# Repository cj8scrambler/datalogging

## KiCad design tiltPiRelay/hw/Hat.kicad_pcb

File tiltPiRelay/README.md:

# TiltPiRelay
Temp controller relay which uses DS18B20 temp sensors and Tilt hydrometers to monitor temperature, control power relays and log data at adafruit.io.  This is intended for a temp controller and data logger for beer fermentation.  It can control 2 seperate fermentations and also monitor internal, ambient and glycol temperatures.  It's written as a python script and intended to run on a Raspberry Pi.

## Hardware

### Relay Board
The controller uses an [off the shelf 4-relay Pi HAT](https://www.amazon.com/gp/product/B072XGF4Z3).  The 4 relays allow for 3 states (Heat/Cold/Off) for each of the two monitored channels.

### LCD / Rotary Encoder / LEDs
The [rotary encoder](https://www.adafruit.com/product/4991) used from Adafruit includes a controller and RGB LED which can be accessed by I2C.  The LCD is a HD44780 based 16x2 I2C display.  All the I2C devices can be daisy chained together.  To simplify the wiring, an interposer HAT was created which adds qwiic connectors.

### Temp sensors
There are 5 one-wire-bus temp sensors supported:
  * Channel 1 - Temperature of fermentation 1 (Used for temp control)
  * Channel 2 - Temperature of fermentation 2 (Used for temp control)
  * Ambient - Ambient air temperature (logged and displayed)
  * Glycol - Glycol reserve temperature (logged and displayed)
  * Internal - Internal temperature on the HAT interposer

Each temp sensor is expected to be on it's own bus (GPIO).  This way there is no need to figure out the address of each sensor.  A 3.5mm stereo headset connector is used to make the temperature probes removeable.

### Connector Interposer
An interposer board simplifies connecting the 1-wire bus temp sensors and I2C deices.  Design files:
  * [Schematic](hw/schematic.pdf) PDF
  * KiCAD design files
    * [Project](hhw/Hat.kicad_pro)
    * [Schematic](hw/Hat.kicad_sch)
    * [PCB](h2/Hat.kicad_pcb)

### Assembly
Inside assembly without high voltage connected

## Software

### One time setup
The dependent Python packages need to be available.  One way to do that is with a virtual env:
```
sudo apt-get install python3-dev
python3 -m venv .venv
. ./.venv/bin/activate
pip3 install --upgrade pip setuptools wheel 
pip3 install -r requirements.txt

. ./.venv/bin/activate
CFLAGS="-fcommon"  pip3 install RPi.GPIO
```

### BLE Support
To receive Tilt hydrometer data, you'll need a BLE capable bluetooth controller.  The Tilt hydrometer sends data in repeated BLE advertisements.  As of September 2024, the bleak packaged should receive these correctly.

On older setups, repeated BLE advertisements would not be reported by bleak.  The workaround was to use hcidump, but this required [special configuration](https://github.com/adafruit/Adafruit_Blinka_bleio#support-for-duplicate-advertisement-scanning-on-linux) so that a regular user can run hcidump.  If you don't see any Tilt data coming in, make sure your user has permissions to run hcidump.

### Load w1 busses
The 5 W1 busses need to be started in order so that the script knows which bus is which temp sensor.  This can be done with `w1-setup.sh load` or manuall done with:
```
sudo dtoverlay w1-gpio gpiopin=23 pullup=0  # CTRL-1  (top left)
sudo dtoverlay w1-gpio gpiopin=27 pullup=0  # CTRL-2  (top right)
sudo dtoverlay w1-gpio gpiopin=17 pullup=0  # AMBIENT (top middle)
sudo dtoverlay w1-gpio gpiopin=24 pullup=0  # GLYCOL  (bottom middle)
sudo dtoverlay w1-gpio gpiopin=25 pullup=0  # ONBOARD
```

### Start at boot
A simple systemd service is defined to auto-start at boot.  Install it with:
```
sudo cp tiltpirelay.service /usr/lib/systemd/system/
sudo systemctl enable tiltpirelay
```

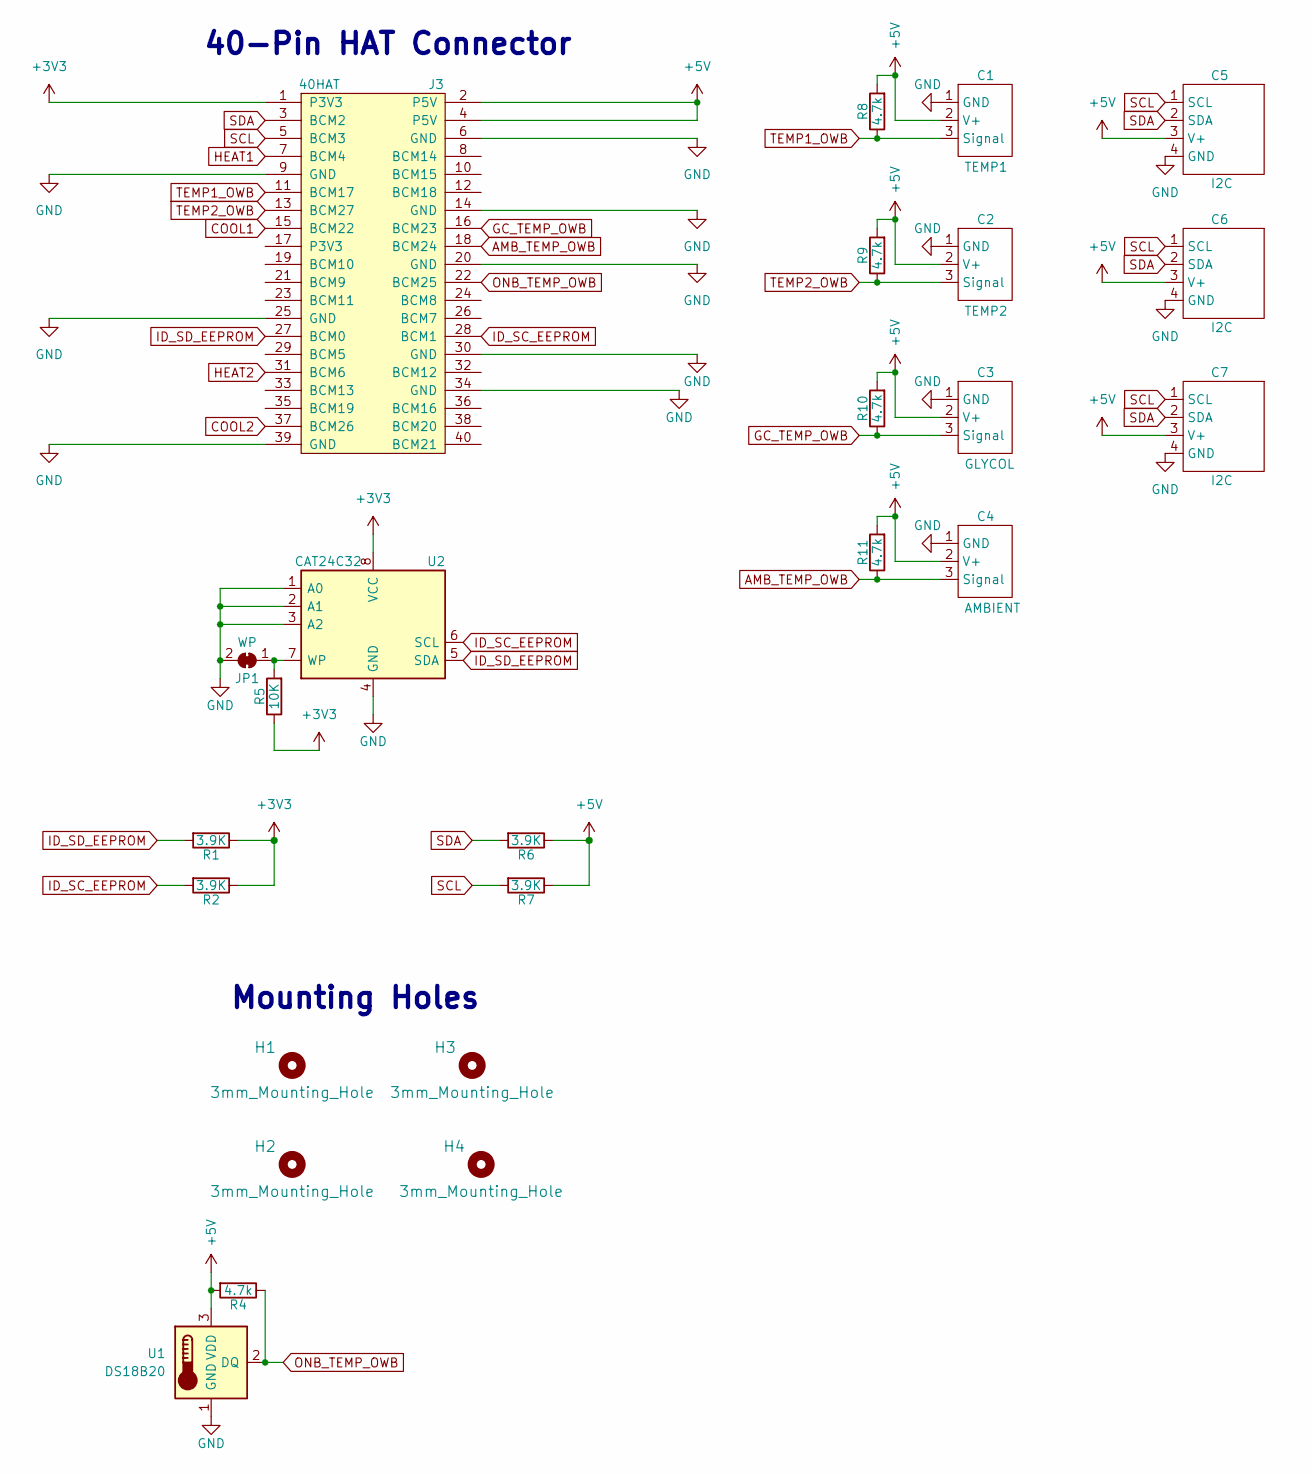
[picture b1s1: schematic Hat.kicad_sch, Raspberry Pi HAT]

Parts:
C1: TEMP1; JST_PH_S3B-PH-SM4-TB_1x03-1MP_P2.00mm_Horizontal
C2: TEMP2; JST_PH_S3B-PH-SM4-TB_1x03-1MP_P2.00mm_Horizontal
C3: GLYCOL; JST_PH_S3B-PH-SM4-TB_1x03-1MP_P2.00mm_Horizontal
C4: AMBIENT; JST_PH_S3B-PH-SM4-TB_1x03-1MP_P2.00mm_Horizontal
C5, C6, C7: I2C; JST_PH_S4B-PH-SM4-TB_1x04-1MP_P2.00mm_Horizontal
H1, H2, H3, H4: 3mm_Mounting_Hole; NPTH_3mm_ID
J3: 40HAT; PinSocket_2x20_P2.54mm_Vertical
JP1: WP; SolderJumper-2_P1.3mm_Bridged_Pad1.0x1.5mm
R1, R2, R6, R7: 3.9K; R_0603_1608Metric
R4, R8, R9, R10, R11: 4.7k; R_0603_1608Metric
R5: 10K; R_0603_1608Metric
U1: DS18B20; TO-92_Inline
U2: CAT24C32; SOIC-8_3.9x4.9mm_P1.27mm

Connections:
+3V3: J3.1 (P3V3), R1.1, R2.1, R5.1, U2.8 (VCC)
+5V: C1.2 (V+), C2.2 (V+), C3.2 (V+), C4.2 (V+), C5.3 (V+), C6.3 (V+), C7.3 (V+), J3.2 (P5V), J3.4 (P5V), R4.2, R6.1, R7.1, R8.2, R9.2, R10.2, R11.2, U1.3 (VDD)
AMB_TEMP_OWB: C4.3 (Signal), J3.18 (BCM24), R11.1
COOL1: J3.15 (BCM22)
COOL2: J3.37 (BCM26)
GC_TEMP_OWB: C3.3 (Signal), J3.16 (BCM23), R10.1
GND: C1.1 (GND), C2.1 (GND), C3.1 (GND), C4.1 (GND), C5.4 (GND), C6.4 (GND), C7.4 (GND), J3.6 (GND), J3.9 (GND), J3.14 (GND), J3.20 (GND), J3.25 (GND), J3.30 (GND), J3.34 (GND), J3.39 (GND), JP1.2 (B), U1.1 (GND), U2.1 (A0), U2.2 (A1), U2.3 (A2), U2.4 (GND)
HEAT1: J3.7 (BCM4)
HEAT2: J3.31 (BCM6)
ID_SC_EEPROM: J3.28 (BCM1), R2.2, U2.6 (SCL)
ID_SD_EEPROM: J3.27 (BCM0), R1.2, U2.5 (SDA)
unnamed: JP1.1 (A), R5.2, U2.7 (WP)
ONB_TEMP_OWB: J3.22 (BCM25), R4.1, U1.2 (DQ)
SCL: C5.1 (SCL), C6.1 (SCL), C7.1 (SCL), J3.5 (BCM3), R7.2
SDA: C5.2 (SDA), C6.2 (SDA), C7.2 (SDA), J3.3 (BCM2), R6.2
TEMP1_OWB: C1.3 (Signal), J3.11 (BCM17), R8.1
TEMP2_OWB: C2.3 (Signal), J3.13 (BCM27), R9.1

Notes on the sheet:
40-Pin HAT Connector
Mounting Holes

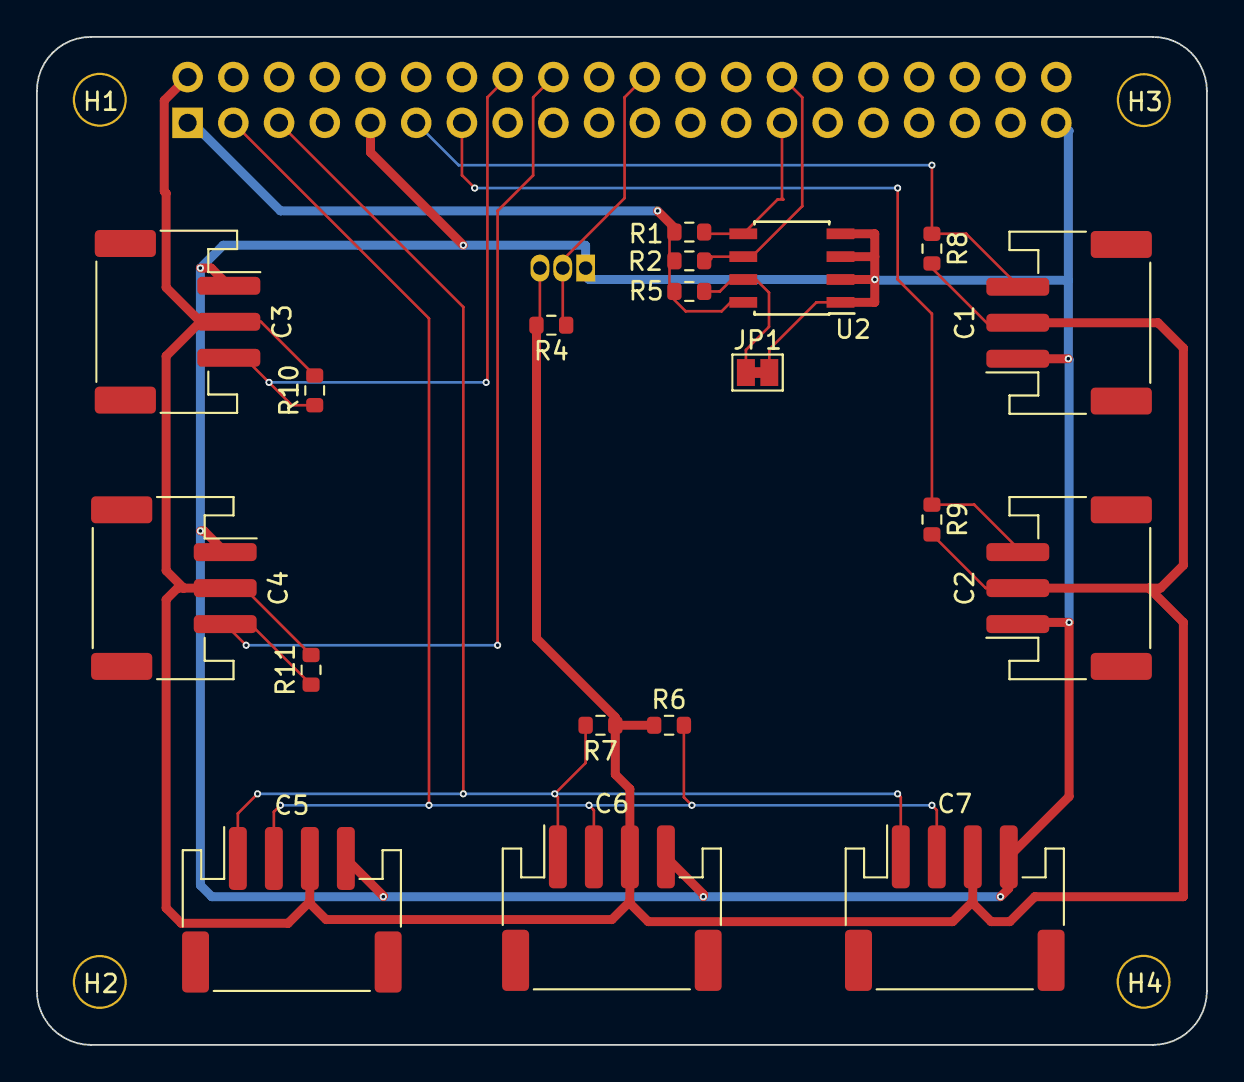
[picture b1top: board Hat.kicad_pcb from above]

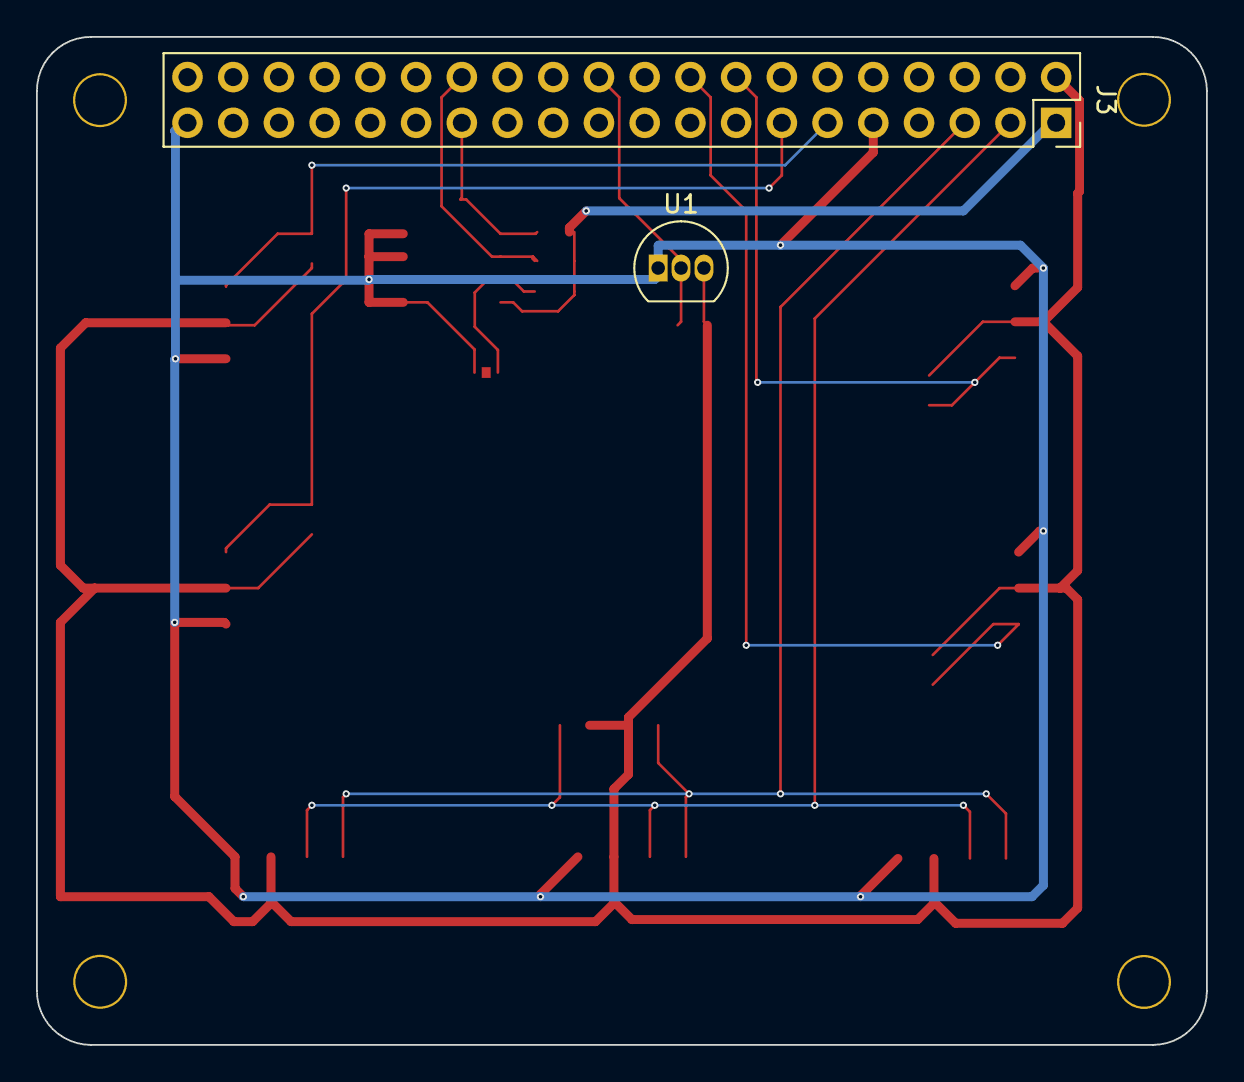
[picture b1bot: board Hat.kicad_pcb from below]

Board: 2 copper layers, 65.0 x 56.0 mm, 25 parts (2 on the bottom side), 13 nets.

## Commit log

2020-12-15 Add luminary maping script
    Python script to convert data from a Google Sheets spreadsheet
    to a KML file.
2020-12-27 dht to adafruit.io data logger
2020-12-27 Greenhouse logging firmware v1.0
    Log data on ESP8266 Huzzah with the following sensors to adafruit.io:
    VEML6075 - UV sensor (discontinued)
    BMP388 - Temp / Pressure
    DHT22 - Temp / Humidity
2020-12-27 Greenhouse feather daugher board V1.0
    Huzzah feather daughter board to hold sensors.
2020-12-27 Updates for VEML
    Configure with default coeficients; log UV-A and UV-B
2020-12-27 Update batt voltage reading
    Update battery voltage reading on A0 using real resistor divider
    values.
2020-12-27 Update the greenhouse datalogger README
2021-11-23 Updates for 2021
2022-02-10 Tilt Pi Relay
    Add baseline work for a Pi based temp controller which reads Tilt
    Hydrometer data and logs everything to adafruit.io
2022-10-31 Final updates from 2021
2022-12-23 Add a gitignore
2022-12-23 Update to later packages
2023-01-24 Big rewrite - functional
    Functional 2-channel relay based temperature controller for beer
    fermentation. Temperature is sensed and logged from one-wire-bus
    temp sensors. GPIOs turn relays on/off to heat or cool. 3 other
    temperatures are also logged for internal, ambient and glycol.
    A basic UI is implemented with serial LCDs and rotary encoders.
    Any nearby Tilt hyrdometers are also logged from their BLE advertisements.
2023-09-05 tiltPiRelay: Add hardware description
2023-09-16 Cleanup logging, documentation and install
    - Clean up the logging mechanisms so modules can be logged at different
    levels.
    - Fix various comments describing the hardware.
    - Create a script to setup / takedown one-wire busses
    - Create a systemd service to start script at boot
    - Update packages
2023-09-17 Fix initial LCD update when temp sensors missing
2023-09-17 Cleanup shutdown and error handling
    - Make sure everything is turned off at exit.
    - Make systemctl service handle failures more robustly
    - Remove logfile accidently checked in.
2023-09-24 Scale heat/cool values for AIO
    AIO can't do dual Y axis plot, so scale the heat / cool values to
    something closer to the expected temp range so the graph is readable.
